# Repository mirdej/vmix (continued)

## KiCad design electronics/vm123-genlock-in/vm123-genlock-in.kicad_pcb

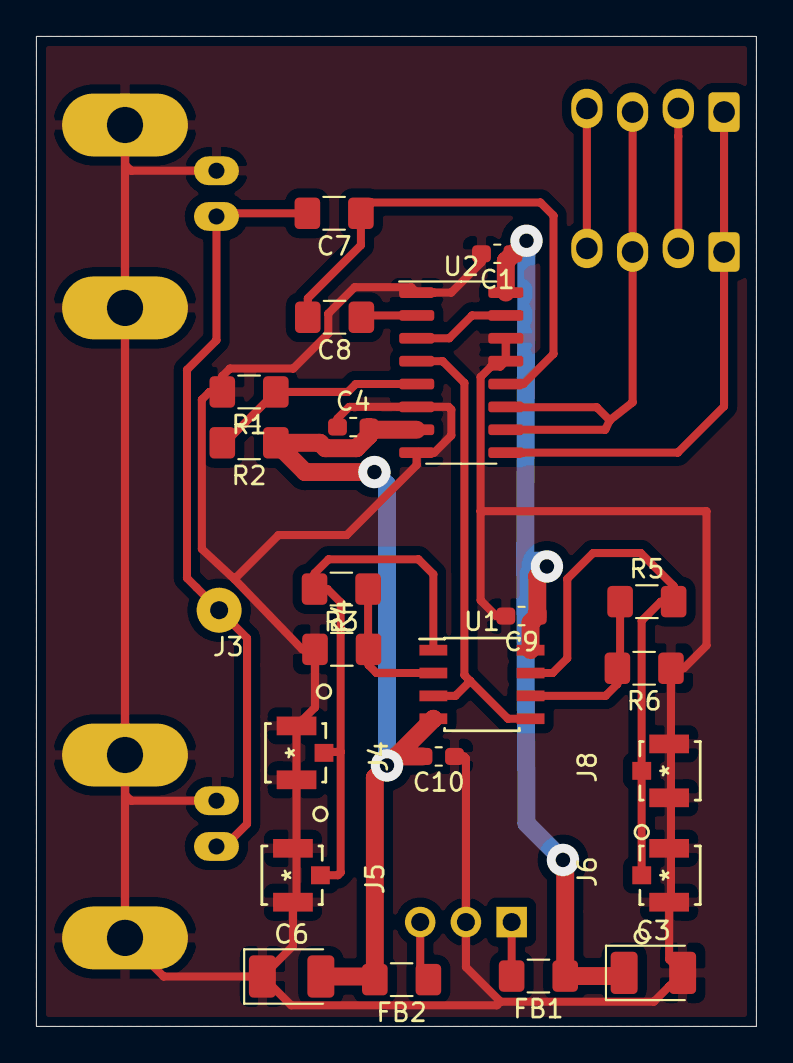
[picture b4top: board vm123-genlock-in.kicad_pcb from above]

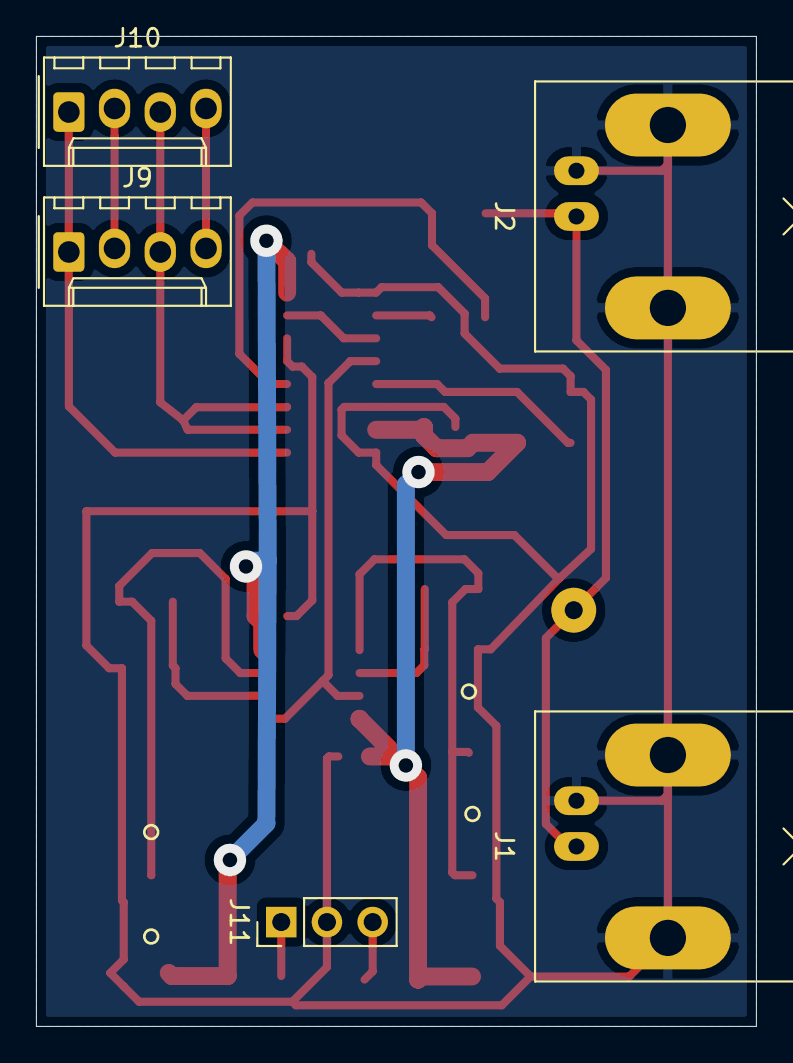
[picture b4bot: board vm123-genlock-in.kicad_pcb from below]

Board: 2 copper layers, 40.0 x 55.0 mm, 28 parts (5 on the bottom side), 19 nets.

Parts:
C1, C4, C9, C10: C; C_0603_1608Metric_Pad1.05x0.95mm_HandSolder
C3, C6: CP; CP_EIA-3528-21_Kemet-B_Pad1.50x2.35mm_HandSolder
C7, C8: 1u; C_1206_3216Metric_Pad1.42x1.75mm_HandSolder
FB1, FB2: Ferrite_Bead; L_1206_3216Metric_Pad1.42x1.75mm_HandSolder
J1, J2: Conn_Coaxial; BNC_MOLEX_0731000080_Horizontal
J3: GENLOCK IN; Solderpad_1mm
J4, J5, J6, J8: UMCC; TE_UMCC_2337019-1
J9, J10: Conn_01x04; Molex_KK-254_AE-6410-04A_1x04_P2.54mm_Vertical
J11: Conn_01x03; PinHeader_1x03_P2.54mm_Vertical
R1: 150; R_1206_3216Metric_Pad1.42x1.75mm_HandSolder
R2: 4k7; R_1206_3216Metric_Pad1.42x1.75mm_HandSolder
R3, R4, R5, R6: 200; R_1206_3216Metric_Pad1.42x1.75mm_HandSolder
U1: MAX4392; SOIC-8_3.9x4.9mm_P1.27mm
U2: 4053; SOIC-16_3.9x9.9mm_P1.27mm

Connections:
+5V: C1.1, C3.1, C9.1, FB1.1, U1.8, U2.16
-5V: C4.2, C6.2, C10.2, FB2.2, R2.1, U1.4, U2.7
/genlock-input: C7.2, J1.1, J2.1, J3.1
/hsync: J9.1, J10.1, U2.9
/oe: J9.4, J10.4
/porch: J9.3, J10.3, U2.10, U2.11
/synctip: R1.1, R2.2, U2.5
/vsync: J9.2, J10.2
GND: C1.2, C3.2, C4.1, C6.1, C9.2, C10.1, J1.2, J2.2, J4.2, J4.3, J5.2, J5.3, J6.2, J6.3, J8.2, J8.3, J11.2, R1.2, R4.1, R6.1, U2.1, U2.6, U2.8, U2.13, U2.14
unnamed: C7.1, C8.2, U2.12
unnamed: C8.1, U2.2
unnamed: FB1.2, J11.1
unnamed: FB2.1, J11.3
unnamed: J4.1, J5.1, R3.2, U1.1
unnamed: J6.1, J8.1, R5.2, U1.7
unnamed: R3.1, R4.2, U1.2
unnamed: R5.1, R6.2, U1.6
unnamed: U1.3, U1.5, U2.4
unnamed: U2.3, U2.15

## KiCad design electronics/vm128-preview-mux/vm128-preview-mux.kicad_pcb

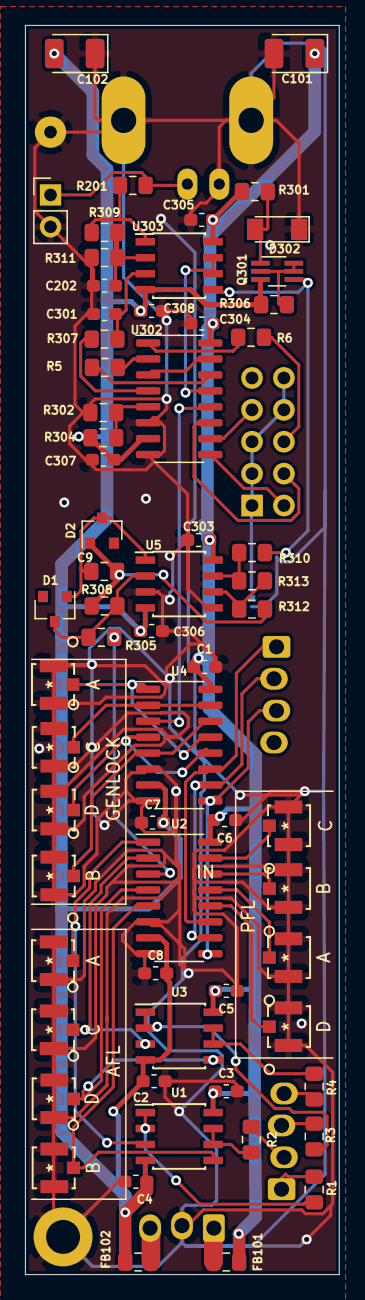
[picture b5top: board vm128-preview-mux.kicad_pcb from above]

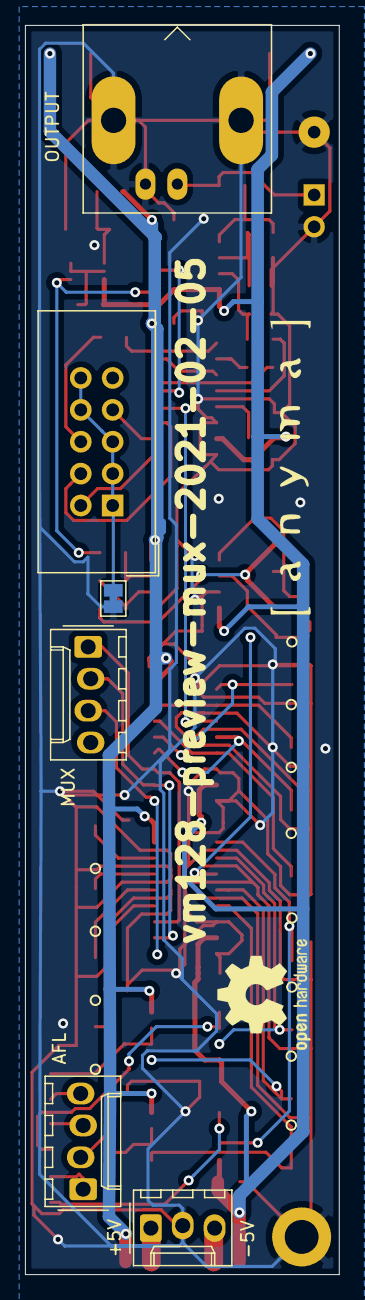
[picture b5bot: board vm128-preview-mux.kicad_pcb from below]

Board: 2 copper layers, 25.0 x 99.5 mm, 74 parts (8 on the bottom side), 54 nets.

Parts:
C1, C2, C3, C4, C303, C304, C305, C306, C307, C308: 100n; C_0603_1608Metric_Pad1.05x0.95mm_HandSolder
C5, C6, C7, C8: C; C_0603_1608Metric_Pad1.05x0.95mm_HandSolder
C9: 1n; C_0805_2012Metric_Pad1.15x1.40mm_HandSolder
C101, C102: 10u; CP_EIA-3528-21_Kemet-B_Pad1.50x2.35mm_HandSolder
C202: 10p; C_0603_1608Metric_Pad1.05x0.95mm_HandSolder
C301: 120p; C_0603_1608Metric_Pad1.05x0.95mm_HandSolder
D1, D2: BAT54; D_SOT-23_ANK
D302: D; D_MiniMELF
FB101, FB102: 330u; L_0805_2012Metric_Pad1.15x1.40mm_HandSolder
H1: MountingHole_Pad; MountingHole_2.7mm_M2.5_DIN965_Pad
J1, J19: Conn_01x04; Molex_KK-254_AE-6410-04A_1x04_P2.54mm_Vertical
J5, J6, J7, J8, J9, J10, J11, J12, J13, J14, J15, J16: UMCC; TE_UMCC_2337019-1
J17: Conn_Coaxial; BNC_MOLEX_0731000080_Horizontal
J18: OUT; PinHeader_1x02_P2.54mm_Vertical
J103: Power; Molex_KK-254_AE-6410-03A_1x03_P2.54mm_Vertical
J104: gnd; Solderpad_1mm
J105: SYNC-BUS; IDC-Header_2x05_P2.54mm_Vertical
JP2: Jumper_NC_Small; SolderJumper-2_P1.3mm_Bridged_Pad1.0x1.5mm
Q301: PMBT3906YS; SOT-363_SC-70-6_Handsoldering
R1, R2, R3, R4, R201, R305, R308, R312, R313: 75; R_0805_2012Metric_Pad1.15x1.40mm_HandSolder
R5: 100; R_0805_2012Metric_Pad1.15x1.40mm_HandSolder
R6: 200; R_0805_2012Metric_Pad1.15x1.40mm_HandSolder
R301, R307: 120; R_0805_2012Metric_Pad1.15x1.40mm_HandSolder
R302: 300; R_0805_2012Metric_Pad1.15x1.40mm_HandSolder
R304: 4k7; R_0805_2012Metric_Pad1.15x1.40mm_HandSolder
R306: 5k6; R_0805_2012Metric_Pad1.15x1.40mm_HandSolder
R309, R311: 220; R_0805_2012Metric_Pad1.15x1.40mm_HandSolder
R310: 330; R_0805_2012Metric_Pad1.15x1.40mm_HandSolder
U1, U3: MAX4392; SOIC-8_3.9x4.9mm_P1.27mm
U2, U4: 4051; SOIC-16_3.9x9.9mm_P1.27mm
U5, U303: LMH6643; SOIC-8_3.9x4.9mm_P1.27mm
U6: LOGO; logo_anyma
U7: LOGO; OSHW-Logo2_9.8x8mm_SilkScreen
U302: 4053; SOIC-16_3.9x9.9mm_P1.27mm

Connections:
+5V: C1.1, C3.1, C5.2, C6.2, C101.1, C303.2, C304.2, C305.2, FB101.2, R301.2, U1.8, U2.16, U3.8, U4.16, U5.8, U302.16, U303.8
-5V: C2.2, C4.2, C7.2, C8.2, C102.2, C306.1, C307.1, C308.1, FB102.2, Q301.3, R304.2, R306.1, U1.4, U2.7, U3.4, U4.7, U5.4, U302.7, U303.4
/Resyncer/GENLOCK: U4.3, U302.12
/Resyncer/INPUT: R305.2, U2.3
/Resyncer/clipper_out: U302.13, U303.6, U303.7
/Resyncer/synctip: R302.2, R304.1, U302.5
/afl1: J5.1, U1.3, U2.1
/afl2: J8.1, U1.5, U2.5
/afl3: J11.1, U2.2, U3.3
/afl4: J14.1, U2.4, U3.5
/burst1: J7.1, U4.1, U4.13
/burst2: J10.1, U4.5, U4.14
/burst3: J13.1, U4.2, U4.15
/burst4: J16.1, U4.4, U4.12
/mux1: J19.1, U2.11, U4.11
/mux2: J19.2, U2.10, U4.10
/mux3: J19.3, U2.9, U4.9
/pfl1: J6.1, U2.13
/pfl2: J9.1, U2.14
/pfl3: J12.1, U2.15
/pfl4: J15.1, U2.12
/supply+: FB101.1, J103.1
/supply-: FB102.1, J103.3
GND: C1.2, C2.1, C3.2, C4.1, C5.1, C6.1, C7.1, C8.1, C101.2, C102.1, C202.2, C301.2, C303.1, C304.1, C305.1, C306.2, C307.2, C308.2, D302.1, H1.1, J5.2, J5.3, J6.2, J6.3, J7.2, J7.3, J8.2, J8.3, J9.2, J9.3, J10.2, J10.3, J11.2, J11.3, J12.2, J12.3, J13.2, J13.3, J14.2, J14.3, J15.2, J15.3, J16.2, J16.3, J17.2, J18.2, J103.2, J104.1, JP2.1, R302.1, R311.1, U2.6, U2.8, U4.6, U4.8, U5.3, U5.5, U302.6, U302.8
unnamed: C9.1, D1.2, D2.1, U5.1
unnamed: C9.2, D2.2, R308.1, R312.2
unnamed: C202.1, R309.2, R311.2, U303.2
unnamed: C301.1, R307.1, U303.3
unnamed: D1.1, R305.1, R308.2, U5.2
unnamed: D302.2, Q301.1, R301.1
unnamed: J1.1, R1.1
unnamed: J1.2, R2.1
unnamed: J1.3, R3.1
unnamed: J1.4, R4.1
unnamed: J17.1, J18.1, R201.2
unnamed: J105.1, J105.3, J105.5, J105.8, J105.10, JP2.2
unnamed: Q301.2, Q301.5, Q301.6, R306.2
unnamed: Q301.4, R310.1, U303.5
unnamed: R1.2, U1.1, U1.2
unnamed: R2.2, U1.6, U1.7
unnamed: R3.2, U3.1, U3.2
unnamed: R4.2, U3.6, U3.7
unnamed: R5.1, U302.2
unnamed: R5.2, U302.14
unnamed: R6.1, U302.1
unnamed: R201.1, R309.1, U303.1
unnamed: R307.2, U302.4
unnamed: R310.2, R313.1, U5.7
unnamed: R312.1, R313.2, U5.6
unnamed: U302.3, U302.15
hsync: J105.2, U302.9
porch: J105.4, U302.11
synkietxt: J105.6, R6.2
synkietxt_enable: J105.7, U302.10

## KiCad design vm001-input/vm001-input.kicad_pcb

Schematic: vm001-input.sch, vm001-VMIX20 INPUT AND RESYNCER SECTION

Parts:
C1, C2: 10u; CP_EIA-3528-21_Kemet-B_Pad1.50x2.35mm_HandSolder
C3, C4, C6, C7, C8, C9, C13, C14, C15, C16, C17, C18, C19: 100n; C_0603_1608Metric_Pad1.05x0.95mm_HandSolder
C5, C11: 10p; C_0805_2012Metric_Pad1.15x1.40mm_HandSolder
C12: 68p; C_1206_3216Metric_Pad1.42x1.75mm_HandSolder
C20: 120p; C_0603_1608Metric_Pad1.05x0.95mm_HandSolder
D2, D4: BAT54S; SOT-23
D3: D; D_MiniMELF
D5: BAT54; D_SOT-23_ANK
FB1, FB2: 330u; L_1206_3216Metric_Pad1.42x1.75mm_HandSolder
H1, H2, H3: MountingHole_Pad; MountingHole_2.7mm_M2.5_ISO7380_Pad
J1: SIFF_IN; Molex_KK-254_AE-6410-02A_1x02_P2.54mm_Vertical
J2: COMPOSITE-INPUT; Molex_KK-254_AE-6410-02A_1x02_P2.54mm_Vertical
J3: Power; Molex_KK-254_AE-6410-03A_1x03_P2.54mm_Vertical
J4: Switch; PinHeader_1x02_P2.54mm_Vertical
J5: INPUT_CLAMPED; Molex_KK-254_AE-6410-02A_1x02_P2.54mm_Vertical
J6: Conn_01x10; IDC-Header_2x05_P2.54mm_Vertical
J7: VIDEO_OUT; Molex_KK-254_AE-6410-02A_1x02_P2.54mm_Vertical
J8: SIFF-INPUT; Solderpad_1mm
Q1: PMBT3906YS; SOT-363_SC-70-6_Handsoldering
Q2: PEMX1; SOT-666
R1, R2, R5, R7, R11, R15, R19, R27, R30: 75; R_0805_2012Metric_Pad1.15x1.40mm_HandSolder
R6, R8, R14, R16, R23, R24: 220; R_0805_2012Metric_Pad1.15x1.40mm_HandSolder
R9, R20: 120; R_0805_2012Metric_Pad1.15x1.40mm_HandSolder
R10: 330; R_0805_2012Metric_Pad1.15x1.40mm_HandSolder
R12: 5k6; R_0805_2012Metric_Pad1.15x1.40mm_HandSolder
R13, R32: 47k; R_0805_2012Metric_Pad1.15x1.40mm_HandSolder
R17: 560; R_0805_2012Metric_Pad1.15x1.40mm_HandSolder
R21, R28, R29, R31: 3k; R_0805_2012Metric_Pad1.15x1.40mm_HandSolder
R22: (75); R_0805_2012Metric_Pad1.15x1.40mm_HandSolder
R25: 300; R_0805_2012Metric_Pad1.15x1.40mm_HandSolder
R26: 4k7; R_0805_2012Metric_Pad1.15x1.40mm_HandSolder
RV1: R_POT_Dual; RK12L123
TP1, TP2, TP3: TestPoint; Solderpad_1mm
U1, U2, U3, U4: LMH6643; SOIC-8_3.9x4.9mm_P1.27mm
U5, U6: 4053; SOIC-16_3.9x9.9mm_P1.27mm

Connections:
+5V: C1.1, C3.2, C6.2, C8.2, C13.2, C16.2, C18.2, D2.2, D4.2, FB1.2, Q2.6, R9.2, R13.1, U1.8 (V+), U2.8 (V+), U3.8 (V+), U4.8 (V+), U5.16 (VDD), U6.16 (VDD)
-5V: C2.2, C4.1, C7.1, C9.1, C14.1, C17.1, C19.1, D2.1, D4.1, FB2.2, Q1.3, R12.1, R26.2, U1.4 (V-), U2.4 (V-), U3.4 (V-), U4.4 (V-), U5.7 (VEE), U6.7 (VEE)
/clamped: R21.1, U5.4 (Z)
/clipper_out: Q1.4, Q2.1, R10.1, U6.1 (Y1)
/colorburst: R2.1, TP2.1, U5.15 (Y)
/delayed_burst: R16.1, TP1.1, U2.1, U6.12 (X0)
/dry: R15.2, U4.6 (-), U4.7, U6.5 (Z0)
/genlock: J6.7, J6.8, R1.1, R22.2
/hsync: J6.2, U5.9 (C), U6.10 (B)
/porch: J6.4, U5.10 (B), U5.11 (A), U6.11 (A)
/synctip: R25.2, R26.1, U6.2 (Y0)
unnamed: C5.1, RV1.3, U2.5 (+)
unnamed: C11.1, RV1.6, U2.3 (+)
unnamed: C12.1, R17.2, U5.2 (Y0)
unnamed: C12.2, U4.1, U4.2 (-)
unnamed: C15.1, U5.3 (Z1), U5.12 (X0)
unnamed: C15.2, R15.1
unnamed: C20.1, R20.1, U1.5 (+)
unnamed: D2.3, R7.2, R11.1
unnamed: D3.2, Q1.1, R9.1
unnamed: D4.3, R30.2, U3.3 (+)
unnamed: D5.1, Q2.2, Q2.3, Q2.5, R13.2
unnamed: FB1.1, J3.1
unnamed: FB2.1, J3.3
unnamed: J1.1, U1.3 (+)
unnamed: J2.1, R5.2, R7.1
unnamed: J4.1, U6.9 (C)
unnamed: J5.1, R19.2
unnamed: J7.1, R27.2
unnamed: J8.1, R30.1, R32.2
unnamed: Q1.2, Q1.5, Q1.6, R12.2
unnamed: R1.2, U4.3 (+)
unnamed: R2.2, R6.2, RV1.1, RV1.2
unnamed: R6.1, R8.2, U2.6 (-)
unnamed: R10.2, U1.1, U1.2 (-)
unnamed: R11.2, U4.5 (+)
unnamed: R14.1, R16.2, U2.2 (-)
unnamed: R8.1, R14.2, RV1.4, RV1.5, U2.7
unnamed: R19.1, R29.2, U3.7
unnamed: R20.2, U6.4 (Z)
unnamed: R21.2, R28.2, U3.5 (+)
unnamed: R23.2, R24.2, U1.6 (-)
unnamed: R24.1, R27.1, U1.7
unnamed: R28.1, U3.1, U3.2 (-)
unnamed: R29.1, R31.1, U3.6 (-)
unnamed: U6.13 (X1), U6.15 (Y)
unnamed: U6.3 (Z1), U6.14 (X)

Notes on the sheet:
PHASE-SHIFTER
CLIPPER
RESYNCER
INPUT-CLAMP AND SPLITTER
goes to vm003-eq
to monitor
from vm003eq-scabi-out

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
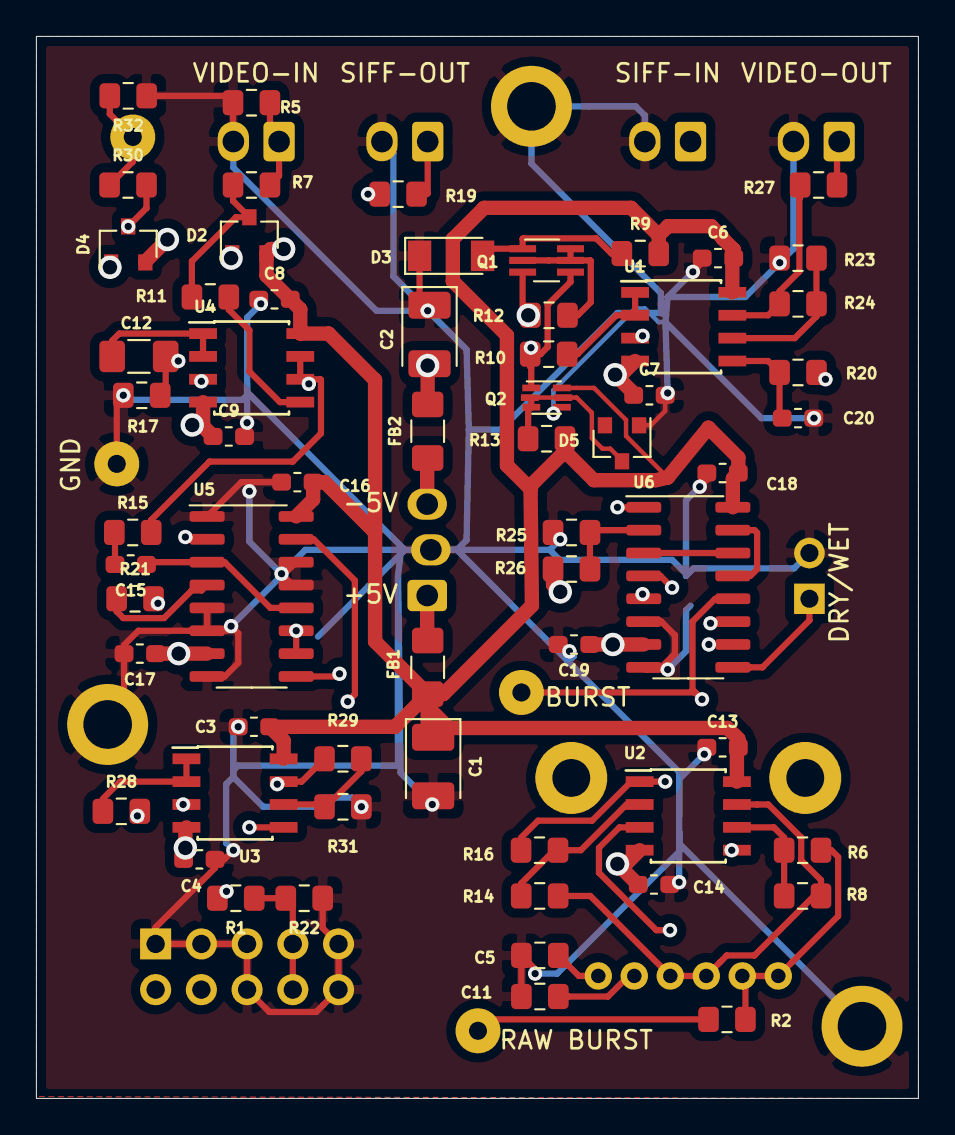
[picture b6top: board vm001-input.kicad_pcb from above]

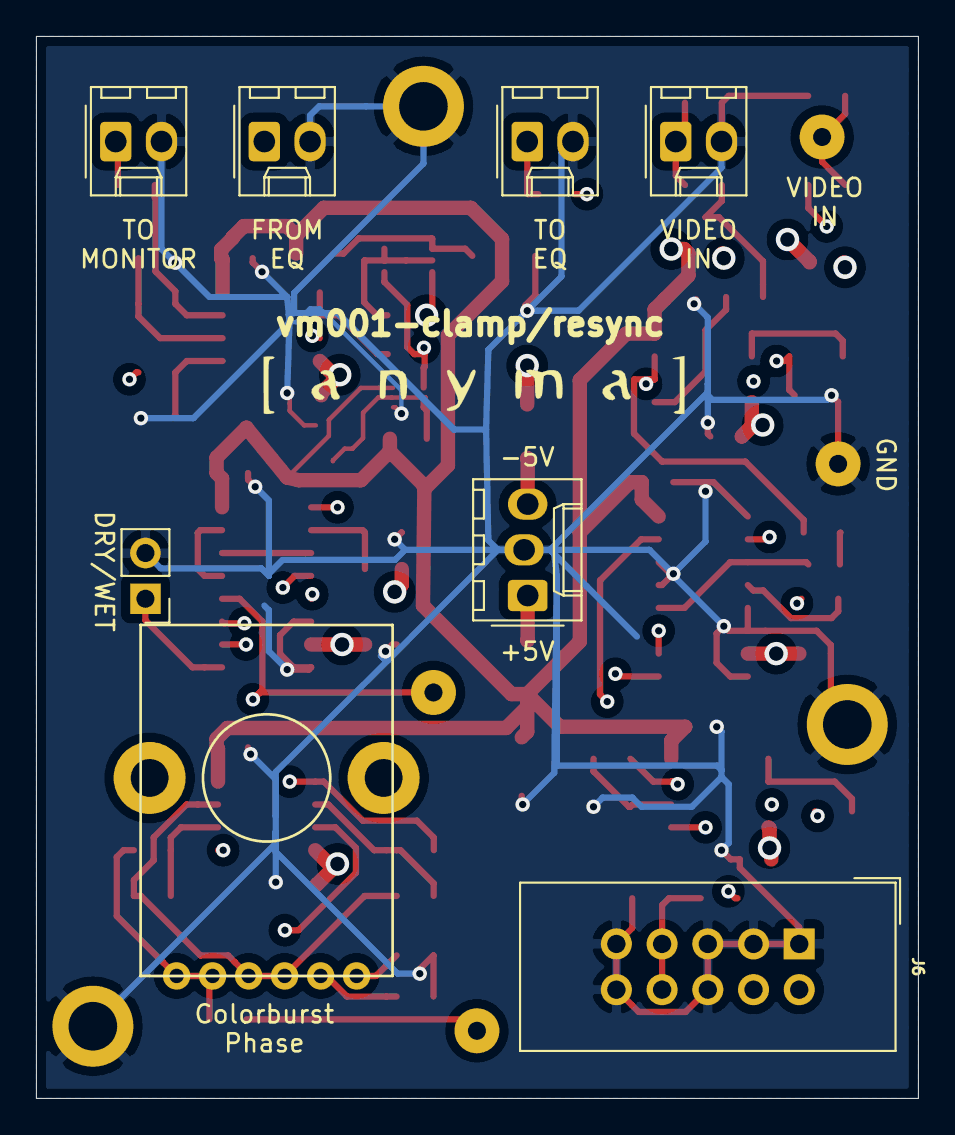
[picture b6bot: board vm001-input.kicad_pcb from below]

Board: 4 copper layers, 49.0 x 59.0 mm, 77 parts (8 on the bottom side), 48 nets.

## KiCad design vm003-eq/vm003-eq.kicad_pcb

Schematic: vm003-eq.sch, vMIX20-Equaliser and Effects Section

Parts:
C1, C2, C3, C4, C8, C9, C10, C11, C12, C13, C101, C102, C106, C108: 100n; C_0603_1608Metric_Pad1.05x0.95mm_HandSolder
C5: 2u; C_1206_3216Metric_Pad1.42x1.75mm_HandSolder
C6: 1u; C_1206_3216Metric_Pad1.42x1.75mm_HandSolder
C7: 100p; C_1206_3216Metric_Pad1.42x1.75mm_HandSolder
C14: 1n; C_0805_2012Metric_Pad1.15x1.40mm_HandSolder
C15: 100p; C_0805_2012Metric_Pad1.15x1.40mm_HandSolder
C16, C17, C18, C19: 10u; CP_EIA-3528-21_Kemet-B_Pad1.50x2.35mm_HandSolder
C105, C107: 4u7; CP_EIA-3528-21_Kemet-B_Pad1.50x2.35mm_HandSolder
D1: D; D_MiniMELF
D2: BAT54; D_SOT-23_ANK
D101, D102: BAT54S; SOT-23
FB1, FB2: Ferrite_Bead; L_0805_2012Metric_Pad1.15x1.40mm_HandSolder
J1: EQ_IN; Solderpad_1mm
J2: SCABI_IN; Solderpad_1mm
J3: SCABI_OUT; Solderpad_1mm
J4: OUTPUT; Molex_KK-254_AE-6410-02A_1x02_P2.54mm_Vertical
J5: INVERTER-DROP; Solderpad_1mm
J6: Conn_01x10; IDC-Header_2x05_P2.54mm_Vertical
J7: COMPA-DROP; Solderpad_1mm
J8: INPUT; Molex_KK-254_AE-6410-02A_1x02_P2.54mm_Vertical
J9: EDGES_IN; Solderpad_1mm
J10: LEVEl_METER; Solderpad_1mm
J11: gnd; Solderpad_1mm
J12: EDGES_OUT; Solderpad_1mm
J13: EQ_OUT; Solderpad_1mm
J101: Bias_In; Solderpad_1mm
J102: Scale_In; Solderpad_1mm
J107: Supply; Molex_KK-254_AE-6410-03A_1x03_P2.54mm_Vertical
L1: 330u; L_1210_3225Metric_Pad1.42x2.65mm_HandSolder
L2, L3: 1.19uH; L_1210_3225Metric_Pad1.42x2.65mm_HandSolder
Q1, Q103: PMBT3906YS; SOT-363_SC-70-6_Handsoldering
Q2: PEMX1; SOT-666
Q101: PNP; SOT-23_BEC
Q102: BC847; SOT-23_BEC
R1, R2, R20, R102, R106, R126: 100; R_0805_2012Metric_Pad1.15x1.40mm_HandSolder
R3, R8, R9: 2k5; R_0805_2012Metric_Pad1.15x1.40mm_HandSolder
R4: 120; R_0805_2012Metric_Pad1.15x1.40mm_HandSolder
R5: 5k6; R_0805_2012Metric_Pad1.15x1.40mm_HandSolder
R6: 330; R_0805_2012Metric_Pad1.15x1.40mm_HandSolder
R7, R101, R103, R105: 47k; R_0805_2012Metric_Pad1.15x1.40mm_HandSolder
R10: 680; R_0805_2012Metric_Pad1.15x1.40mm_HandSolder
R11: 160; R_0805_2012Metric_Pad1.15x1.40mm_HandSolder
R12, R13, R14: 2k2; R_0805_2012Metric_Pad1.15x1.40mm_HandSolder
R15, R16, R127: 75; R_0805_2012Metric_Pad1.15x1.40mm_HandSolder
R17: 16k; R_0805_2012Metric_Pad1.15x1.40mm_HandSolder
R18, R121, R124, R125: 1k; R_0805_2012Metric_Pad1.15x1.40mm_HandSolder
R19: 30k; R_0805_2012Metric_Pad1.15x1.40mm_HandSolder
R21: 15k; R_0805_2012Metric_Pad1.15x1.40mm_HandSolder
R104, R108, R111, R112, R117, R120: 10k; R_0805_2012Metric_Pad1.15x1.40mm_HandSolder
R107: 20k; R_0805_2012Metric_Pad1.15x1.40mm_HandSolder
R109: 100k; R_0805_2012Metric_Pad1.15x1.40mm_HandSolder
R110: 470k; R_0805_2012Metric_Pad1.15x1.40mm_HandSolder
R113, R114: 3k3; R_0805_2012Metric_Pad1.15x1.40mm_HandSolder
R115, R116: 4k7; R_0805_2012Metric_Pad1.15x1.40mm_HandSolder
R122: 300; R_0805_2012Metric_Pad1.15x1.40mm_HandSolder
R123: 560; R_0805_2012Metric_Pad1.15x1.40mm_HandSolder
RV1, RV4, RV5: R_POT; Potentiometer_Alps_RK09K_Single_Horizontal
SW1: HIGH_CLIP; PinHeader_1x02_P2.54mm_Vertical
SW2: LOW_CLIP; PinHeader_1x02_P2.54mm_Vertical
U1, U2, U3, U101: LMH6643; SOIC-8_3.9x4.9mm_P1.27mm
U5: LM311; SOIC-8_3.9x4.9mm_P1.27mm
U6: MAX4053; SOP-16_4.55x10.3mm_P1.27mm
U102: LT1228; SOIC-8_3.9x4.9mm_P1.27mm

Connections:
+5V: C1.2, C3.2, C8.2, C10.2, C12.2, C16.1, C17.1, C101.2, C105.1, C106.2, D101.2, D102.2, FB1.2, Q2.6 (C), R4.1, R7.1, R10.1, R113.1, R117.1, U1.8 (V+), U2.8 (V+), U3.8 (V+), U5.8 (V+), U6.16 (VDD), U101.8 (V+), U102.7 (Vcc)
-5V: C2.1, C4.1, C9.1, C11.1, C13.1, C18.2, C19.2, C102.2, C107.2, C108.2, D101.1, D102.1, FB2.2, Q1.3 (C), R5.2, R17.2, R107.2, R112.2, R114.2, U1.4 (V-), U2.4 (V-), U3.4 (V-), U5.4 (V-), U6.7 (VEE), U101.4 (V-), U102.4 (Vss)
/bias_cv: J6.9, R105.1
/clipper_out: J4.1, J10.1, U2.6 (-), U2.7
/compa_bypass: J6.6, U6.11 (A)
/compa_cv: J6.3, U5.3 (-)
/compa_out: J7.1, R10.2, R11.1, U5.7, U6.13 (X1)
/edges_bypass: J6.5, U6.9 (C)
/edges_in: J8.1, J9.1, R18.2, U6.5 (Z0)
/edges_out: C14.2, J12.1, R20.2, U6.3 (Z1)
/eq_in: J1.1, R1.2, U6.4 (Z)
/eq_out: J13.1, R15.1, R16.2, U5.2 (+), U6.12 (X0)
/inverter_bypass: J6.7, U6.10 (B)
/inverter_in: R13.2, U6.2 (Y0), U6.14 (X)
/inverter_out: J5.1, R14.1, U3.1, U6.1 (Y1)
/scabi_in: J2.1, R120.1, U6.15 (Y)
/scabi_out: J3.1, R127.1, U2.3 (+)
/scale_cv: J6.1, R110.1
GND: C1.1, C2.2, C3.1, C4.2, C8.1, C9.2, C10.1, C11.2, C12.1, C13.2, C15.1, C16.2, C17.2, C18.1, C19.1, C101.1, C102.1, C105.2, C106.1, C107.1, C108.1, D1.1 (K), D2.2 (A), J4.2, J6.2, J6.4, J6.8, J6.10, J8.2, J11.1, J107.2, L1.2, L2.2, L3.2, Q2.4 (E), Q103.2 (B), Q103.4 (E), Q103.6 (C), R8.1, R11.2, R12.1, R16.1, R20.1, R21.2, R101.1, R103.1, R111.1, R121.1, R122.1, R123.1, R126.1, U5.1 (GND), U6.6 (Inh), U6.8 (VSS), U101.3 (+), U101.5 (+)
unnamed: C5.1, RV1.2
unnamed: C5.2, L1.1
unnamed: C6.1, RV4.2
unnamed: C6.2, L2.1
unnamed: C7.1, RV5.2
unnamed: C7.2, L3.1
unnamed: C14.1, R19.1, U3.7
unnamed: C15.2, R18.1, U3.5 (+)
unnamed: D1.2 (A), Q1.1 (E), R4.2
unnamed: D2.1 (K), Q2.2 (B), Q2.3 (C), Q2.5 (B), R7.2
unnamed: D101.3, R102.2, R104.1
unnamed: D102.3, R106.2, R109.1
unnamed: FB1.1, J107.3
unnamed: FB2.1, J107.1
unnamed: J101.1, R101.2, R102.1
unnamed: J102.1, R103.2, R106.1
unnamed: Q1.2 (B), Q1.5 (B), Q1.6 (C), R5.1
unnamed: Q1.4 (E), SW1.1 (A)
unnamed: Q2.1 (E), SW2.2 (B)
unnamed: Q101.B, R108.2, U101.7
unnamed: Q101.C, Q102.C, R122.2, U102.1 (Iout)
unnamed: Q101.E, R113.2
unnamed: Q102.B, R111.2, R112.1
unnamed: Q102.E, R114.1
unnamed: Q103.1 (E), R115.2, R117.2
unnamed: Q103.3 (C), R124.2
unnamed: Q103.5 (B), R116.2, U101.1
unnamed: R1.1, U1.3 (+)
unnamed: R2.1, R3.2, U1.1
unnamed: R2.2, U1.2 (-)
unnamed: R3.1, RV1.3, RV4.3, RV5.3, U1.5 (+)
unnamed: R6.1, SW1.2 (B), SW2.1 (A), U2.5 (+)
unnamed: R6.2, U2.1, U2.2 (-)
unnamed: R8.2, R9.2, RV1.1, RV4.1, RV5.1, U1.6 (-)
unnamed: R12.2, U3.3 (+)
unnamed: R13.1, R14.2, R17.1, U3.2 (-)
unnamed: R9.1, R15.2, U1.7
unnamed: R19.2, R21.1, U3.6 (-)
unnamed: R104.2, R105.2, R107.1, R108.1, U101.6 (-)
unnamed: R109.2, R110.2, R115.1, R116.1, U101.2 (-)
unnamed: R120.2, R121.2, U102.3 (+In)
unnamed: R123.2, U102.2 (-In)
unnamed: R124.1, U102.5 (Iset)
unnamed: R125.1, R127.2, U102.6 (Vout)
unnamed: R125.2, R126.2, U102.8 (Gain)
unnamed: U5.5 (BAL), U5.6 (STRB)

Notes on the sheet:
EQUALISER
We dont have 2k5. Use 2k2 ??
Footprint seems a tad too wide
Bias section
scale section
SCALE-BIAS
CLIPPER
1) EDGES

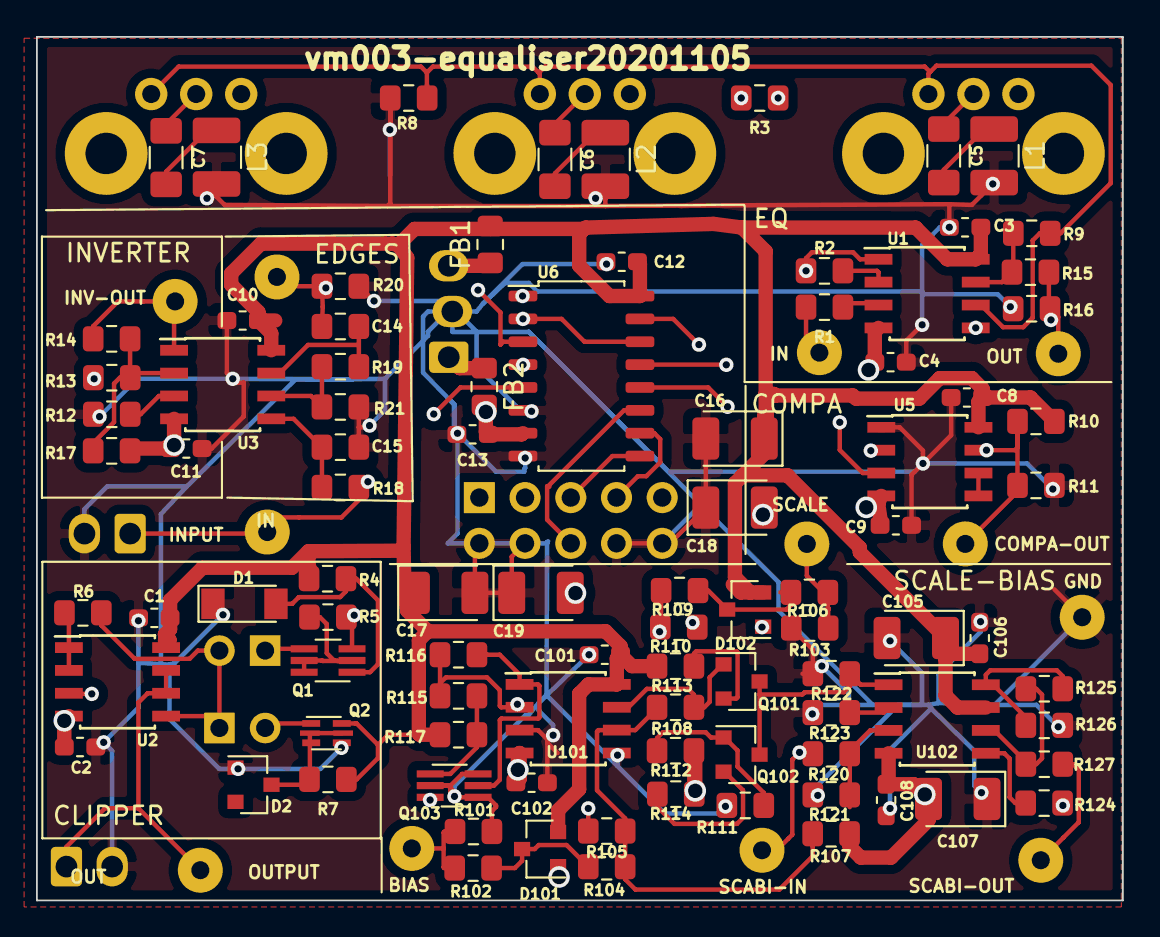
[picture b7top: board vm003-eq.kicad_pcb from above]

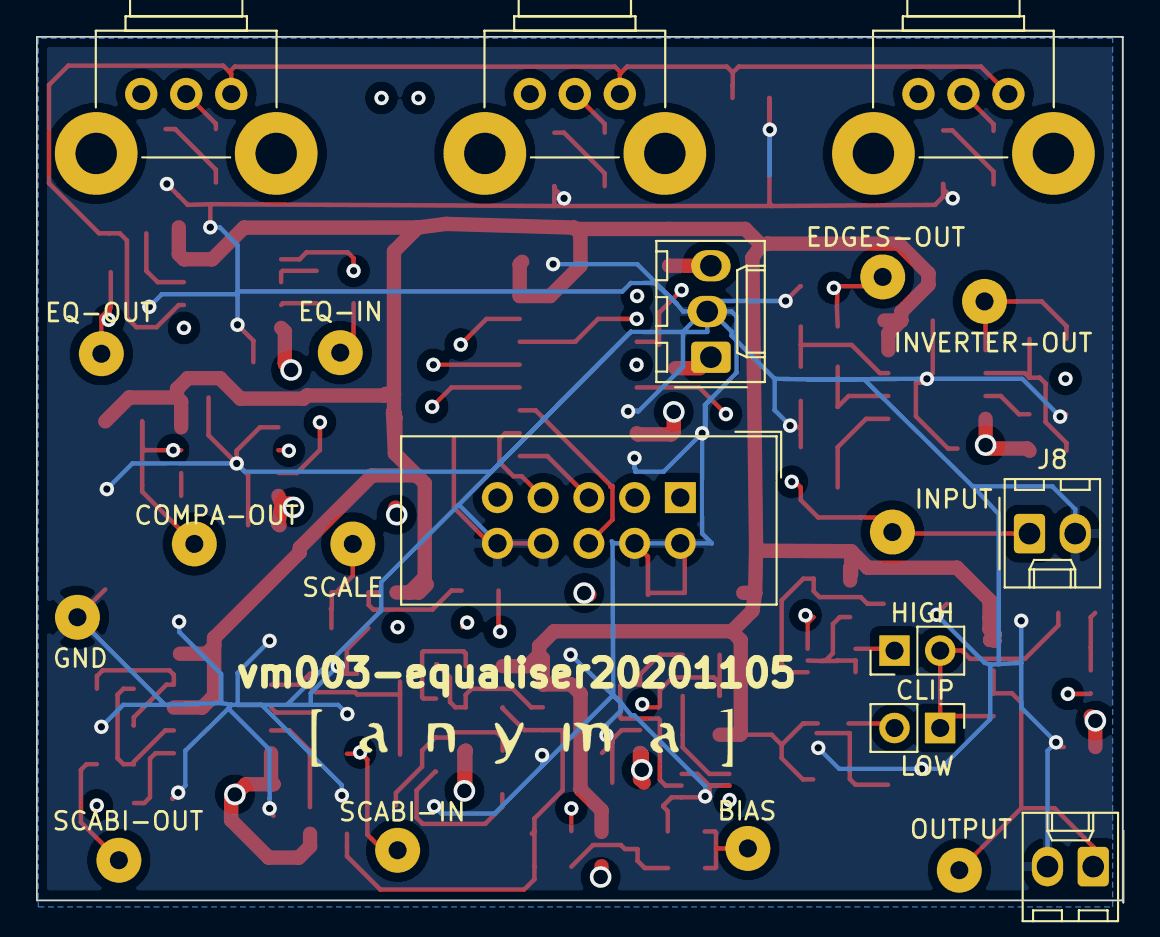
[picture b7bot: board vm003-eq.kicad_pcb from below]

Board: 4 copper layers, 60.3 x 48.0 mm, 113 parts (9 on the bottom side), 65 nets.

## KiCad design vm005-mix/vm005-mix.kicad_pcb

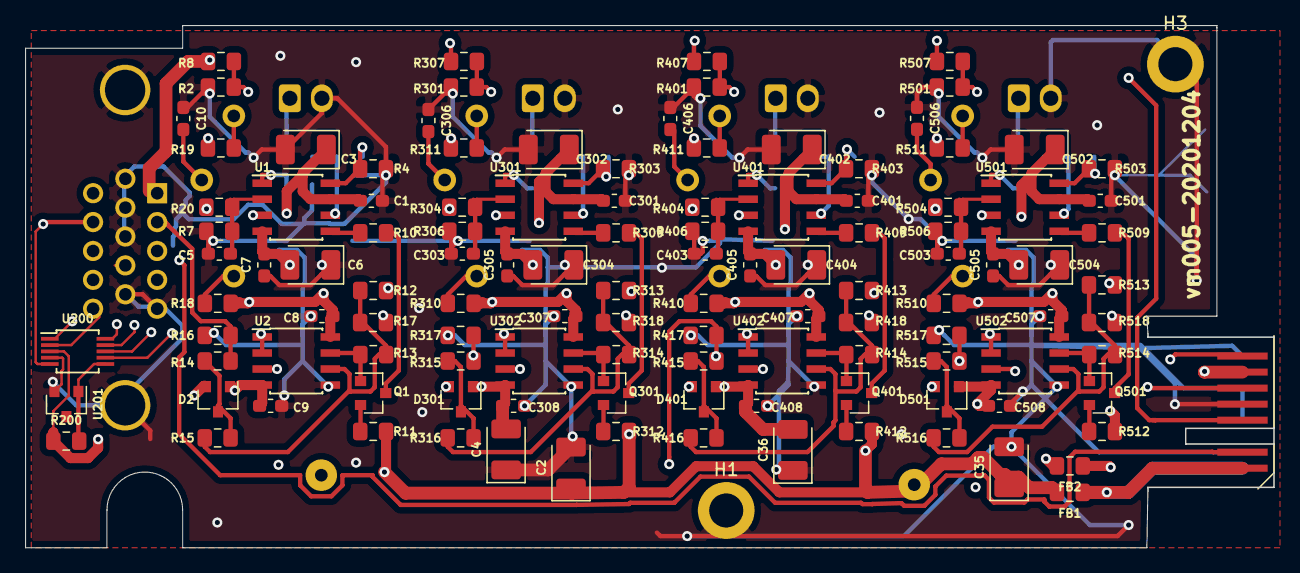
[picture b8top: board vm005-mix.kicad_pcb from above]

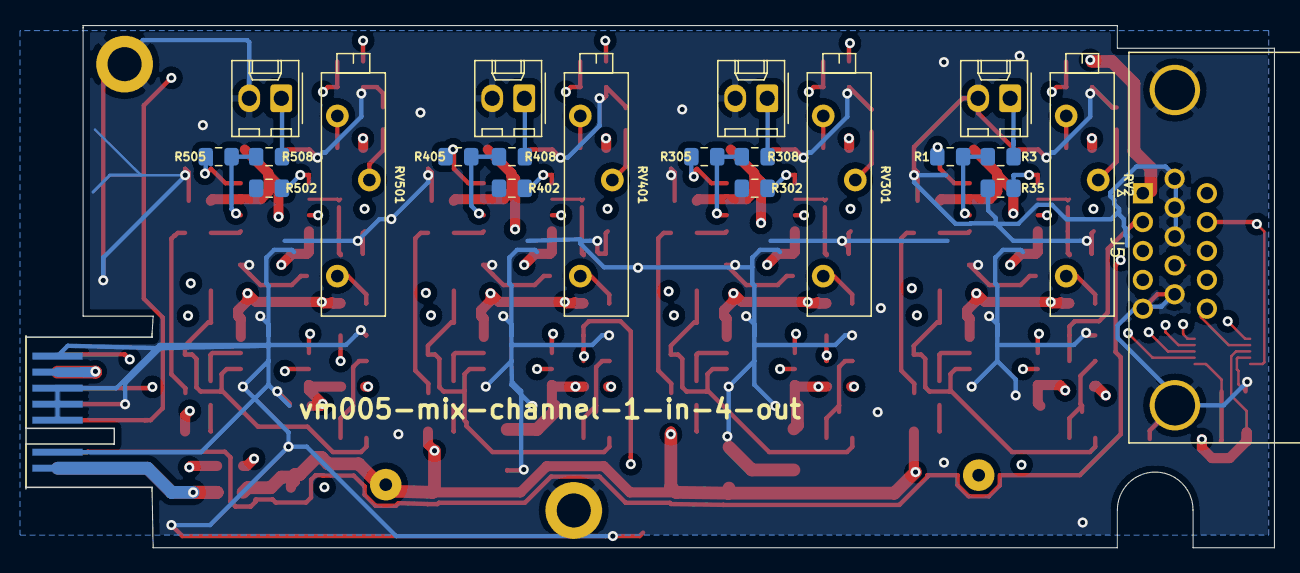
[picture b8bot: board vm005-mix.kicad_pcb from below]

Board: 4 copper layers, 99.0 x 41.4 mm, 144 parts (21 on the bottom side), 82 nets.

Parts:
C1, C7, C8, C9, C301, C305, C307, C308, C401, C405, C407, C408, C501, C505, C507, C508: 100n; C_0603_1608Metric_Pad1.05x0.95mm_HandSolder
C2, C4, C35, C36: 10u; CP_EIA-3528-21_Kemet-B_Pad1.50x2.35mm_HandSolder
C3, C6, C302, C304, C402, C404, C502, C504: 4u7; CP_EIA-3528-21_Kemet-B_Pad1.50x2.35mm_HandSolder
C5, C10, C303, C306, C403, C406, C503, C506: 1u; C_0603_1608Metric_Pad1.05x0.95mm_HandSolder
D2, D301, D401, D501: BAT54S; SOT-23
FB1, FB2: 330u; L_0805_2012Metric_Pad1.15x1.40mm_HandSolder
G1: LOGO; logo_anyma
H1, H3: MountingHole_Pad; MountingHole_2.7mm_M2.5_ISO7380_Pad
J1: Conn_EDGE; Samtec_MECF-08-0_-L-DV_2x08_P1.27mm_Polarized_Edge
J2, J301, J401, J501: Conn_01x02; Molex_KK-254_AE-6410-02A_1x02_P2.54mm_Vertical
J5: DB15_Female_HighDensity_MountingHoles; DSUB-15-HD_Female_FCI
Q1, Q301, Q401, Q501: PNP; SOT-23_BEC
R1, R35, R302, R305, R402, R405, R502, R505: (560); R_0805_2012Metric_Pad1.15x1.40mm_HandSolder
R2, R10, R301, R309, R401, R409, R501, R509: 1k; R_0805_2012Metric_Pad1.15x1.40mm_HandSolder
R3, R308, R408, R508: (75); R_0805_2012Metric_Pad1.15x1.40mm_HandSolder
R4, R303, R403, R503: 120; R_0805_2012Metric_Pad1.15x1.40mm_HandSolder
R7, R8, R14, R306, R307, R315, R406, R407, R415, R506, R507, R515: 100; R_0805_2012Metric_Pad1.15x1.40mm_HandSolder
R11, R312, R412, R512: 2k2; R_0805_2012Metric_Pad1.15x1.40mm_HandSolder
R12, R15, R313, R316, R413, R416, R513, R516: 12K; R_0805_2012Metric_Pad1.15x1.40mm_HandSolder
R13, R314, R414, R514: 20k; R_0805_2012Metric_Pad1.15x1.40mm_HandSolder
R16, R317, R417, R517: 47k; R_0805_2012Metric_Pad1.15x1.40mm_HandSolder
R17, R318, R418, R518: 22k; R_0805_2012Metric_Pad1.15x1.40mm_HandSolder
R18, R19, R20, R304, R310, R311, R404, R410, R411, R504, R510, R511: 3k; R_0805_2012Metric_Pad1.15x1.40mm_HandSolder
R200: 560; R_0805_2012Metric_Pad1.15x1.40mm_HandSolder
RV2, RV301, RV401, RV501: 500; Potentiometer_Bourns_3006P_Horizontal
TP1, TP2: TestPoint; Solderpad_1mm
U1, U301, U401, U501: LT1228; SOIC-8_3.9x4.9mm_P1.27mm
U2, U302, U402, U502: LMH6643; SOIC-8_3.9x4.9mm_P1.27mm
U200: MAX5741; MSOP-10_3x3mm_P0.5mm
U201: ADR510; SOT-23

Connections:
+5V: C1.2, C2.1, C3.1, C8.1, C35.1, C301.2, C302.1, C307.1, C401.2, C402.1, C407.1, C501.2, C502.1, C507.1, D2.2, D301.2, D401.2, D501.2, FB1.2, R11.2, R18.2, R200.1, R310.2, R312.2, R410.2, R412.2, R510.2, R512.2, TP1.1, U1.7, U2.8, U200.3, U301.7, U302.8, U401.7, U402.8, U501.7, U502.8
-5V: C4.2, C6.2, C7.2, C9.1, C36.2, C304.2, C305.2, C308.1, C404.2, C405.2, C408.1, C504.2, C505.2, C508.1, D2.1, D301.1, D401.1, D501.1, FB2.2, R17.1, R19.1, R311.1, R318.1, R411.1, R418.1, R511.1, R518.1, TP2.1, U1.4, U2.4, U301.4, U302.4, U401.4, U402.4, U501.4, U502.4
/cv_a: J5.2, R14.2, R16.2
/cv_b: J5.3, R315.2, R317.2
/cv_c: J5.13, R415.2, R417.2
/cv_d: J5.14, R515.2, R517.2
/dac_a: R12.2, U200.7
/dac_b: R313.2, U200.8
/dac_c: R413.2, U200.9
/dac_d: R513.2, U200.10
/dac_select: J5.9, U200.1
/input: J5.1, R2.2, R301.2, R401.2, R501.2
/mosi: J5.12, U200.5
/out_a: J1.3, R35.2, U1.1
/out_b: J1.7, R302.2, U301.1
/out_c: J1.11, R402.2, U401.1
/out_d: J1.15, R502.2, U501.1
/sck: J5.15, U200.2
/supply+: FB1.1, J1.1, J1.2
/supply-: FB2.1, J1.13, J1.14
GND: C1.1, C2.2, C3.2, C4.1, C5.1, C6.1, C7.1, C8.2, C9.2, C10.1, C35.2, C36.1, C301.1, C302.2, C303.1, C304.1, C305.1, C306.1, C307.2, C308.2, C401.1, C402.2, C403.1, C404.1, C405.1, C406.1, C407.2, C408.2, C501.1, C502.2, C503.1, C504.1, C505.1, C506.1, C507.2, C508.2, H1.1, H3.1, J1.4, J1.8, J1.9, J1.10, J1.12, J1.16, J2.2, J5.0, J5.5, J5.6, J5.7, J5.8, J5.10, J301.2, J401.2, J501.2, R4.2, R7.1, R8.1, R16.1, R35.1, R302.1, R303.2, R306.1, R307.1, R317.1, R402.1, R403.2, R406.1, R407.1, R417.1, R502.1, R503.2, R506.1, R507.1, R517.1, U2.5, U200.4, U201.2, U302.5, U402.5, U502.5
unnamed: C5.2, R7.2, R20.1, U1.2
unnamed: C10.2, RV2.2, U2.3
unnamed: C303.2, R304.1, R306.2, U301.2
unnamed: C306.2, RV301.2, U302.3
unnamed: C403.2, R404.1, R406.2, U401.2
unnamed: C406.2, RV401.2, U402.3
unnamed: C503.2, R504.1, R506.2, U501.2
unnamed: C506.2, RV501.2, U502.3
unnamed: D2.3, R14.1, R15.2
unnamed: D301.3, R315.1, R316.2
unnamed: D401.3, R415.1, R416.2
unnamed: D501.3, R515.1, R516.2
unnamed: J2.1, R3.2
unnamed: J301.1, R308.2
unnamed: J401.1, R408.2
unnamed: J501.1, R508.2
unnamed: Q1.B, R13.1, U2.7
unnamed: Q1.C, R10.1
unnamed: Q1.E, R11.1
unnamed: Q301.B, R314.1, U302.7
unnamed: Q301.C, R309.1
unnamed: Q301.E, R312.1
unnamed: Q401.B, R414.1, U402.7
unnamed: Q401.C, R409.1
unnamed: Q401.E, R412.1
unnamed: Q501.B, R514.1, U502.7
unnamed: Q501.C, R509.1
unnamed: Q501.E, R512.1
unnamed: R1.1, R3.1, U1.6
unnamed: R1.2, R4.1, U1.8
unnamed: R2.1, R8.2, U1.3
unnamed: R10.2, U1.5
unnamed: R12.1, R13.2, R15.1, R17.2, U2.6
unnamed: R18.1, RV2.1
unnamed: R19.2, RV2.3
unnamed: R20.2, U2.1, U2.2
unnamed: R200.2, U200.6, U201.1
unnamed: R301.1, R307.2, U301.3
unnamed: R303.1, R305.2, U301.8
unnamed: R304.2, U302.1, U302.2
unnamed: R305.1, R308.1, U301.6
unnamed: R309.2, U301.5
unnamed: R310.1, RV301.1
unnamed: R311.2, RV301.3
unnamed: R313.1, R314.2, R316.1, R318.2, U302.6
unnamed: R401.1, R407.2, U401.3
unnamed: R403.1, R405.2, U401.8
unnamed: R404.2, U402.1, U402.2
unnamed: R405.1, R408.1, U401.6
unnamed: R409.2, U401.5
unnamed: R410.1, RV401.1
unnamed: R411.2, RV401.3
unnamed: R413.1, R414.2, R416.1, R418.2, U402.6
unnamed: R501.1, R507.2, U501.3
unnamed: R503.1, R505.2, U501.8
unnamed: R504.2, U502.1, U502.2
unnamed: R505.1, R508.1, U501.6
unnamed: R509.2, U501.5
unnamed: R510.1, RV501.1
unnamed: R511.2, RV501.3
unnamed: R513.1, R514.2, R516.1, R518.2, U502.6
